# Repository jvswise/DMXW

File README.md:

# DMXW
DMX-512 wireless gateway to networked Moteino RFM69 (Arduino compatible) based slave devices suitable for running battery operated stage effects up to 300 metres from the gateway.

The gateway allows DMX-512 channels to be be redistributed to low-cost, customizable, battery-operated Moteino based slave nodes. Slaves have 4 analog (PWM) channels that can drive several amps each at 5 -12 Vdc. They have an additional two digital channels. 

There is prototype code, schematics, PCB files, and user manuals:
  - A configurable DMX-512 to DMXW gateway with optional manaul override
    controls (joystick, toggle switches, and potentiometers).
  - A generic remote slave node.
  - A specialized remote slave node for driving an LED pixel strip.
  - A test unit for either remote testing independent of a DMX-512 bus or
    for onboard testing of electronics that are to be connected to a generic
    or pixel strip node.

Folders:
  Arduino_sketches:
    - Arduino sketches for gateway, generic and remote slave nodes, and
      test unit.

  Documentation:
    - User manuals, schematics, PCB files, construction guides.

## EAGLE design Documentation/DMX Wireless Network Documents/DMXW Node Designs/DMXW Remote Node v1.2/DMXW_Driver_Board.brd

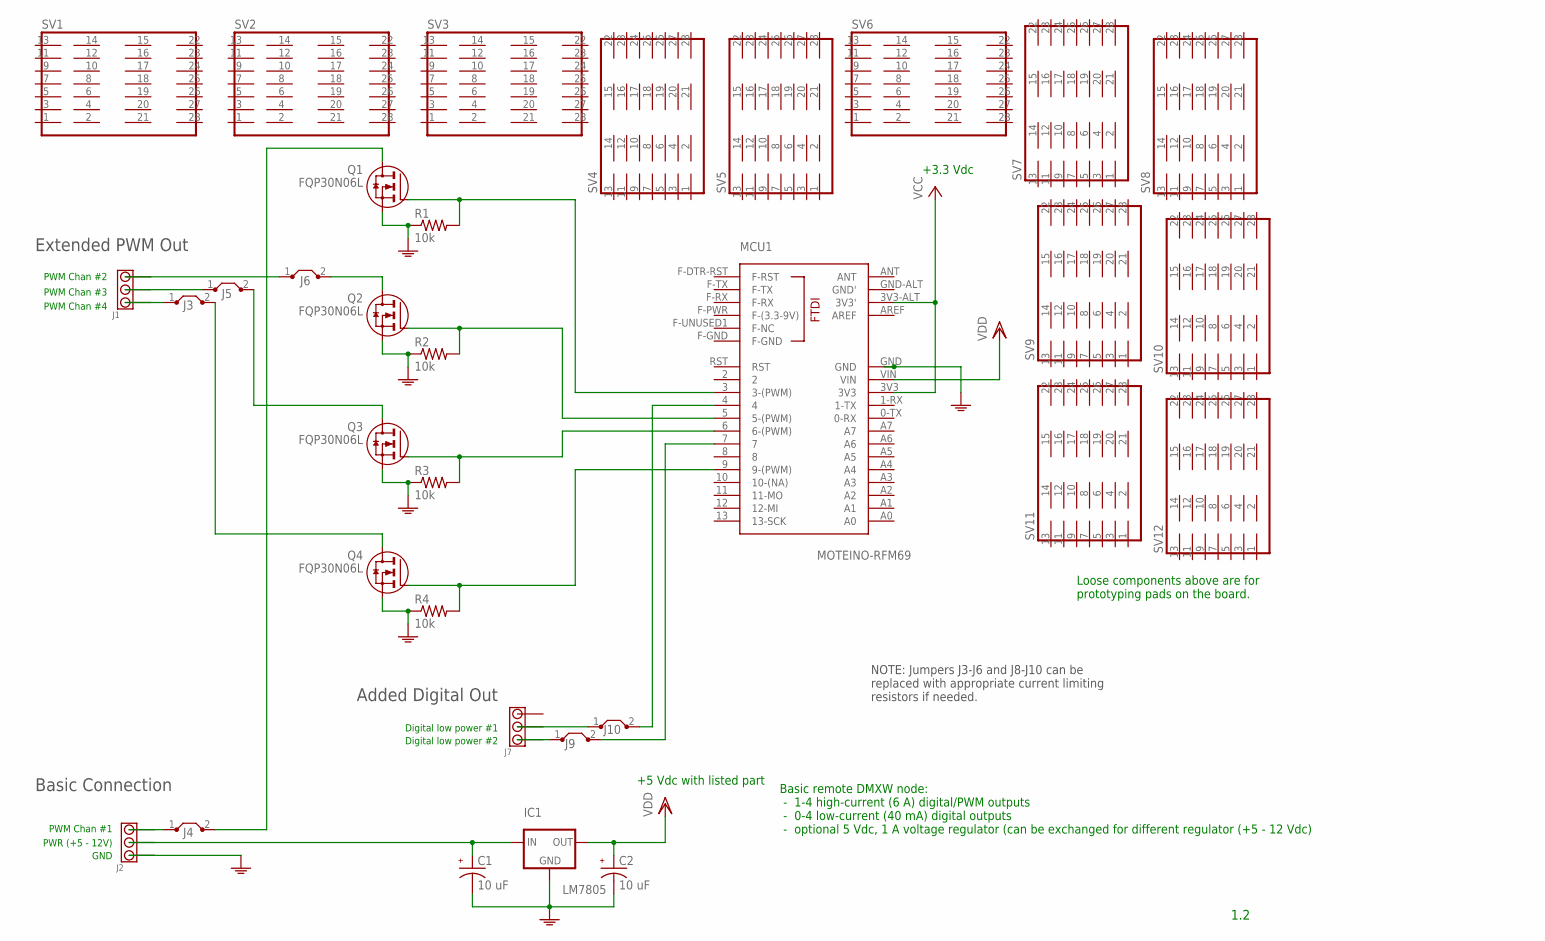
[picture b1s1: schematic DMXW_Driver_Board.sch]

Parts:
C1, C2: 10 uF; RADIAL-CANISTER
IC1: LM7805; TO-220
J1, J2, J7: TERMINAL-BLOCK-3; W237-103
J3, J4, J5, J6, J9, J10: J5MM; 05
MCU1: MOTEINO-RFM69; MOTEINO
Q1, Q2, Q3, Q4: FQP30N06L; TO-220
R1, R2, R3, R4: 10k; 0207/10
SV1, SV2, SV3, SV4, SV5, SV6, SV7, SV8, SV9, SV10, SV11, SV12: 14P

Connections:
GND: C1.-, C2.-, IC1.PIN2 (GND), J2.3, MCU1.GND, Q1.PIN3 (S), Q2.PIN3 (S), Q3.PIN3 (S), Q4.PIN3 (S), R1.1, R2.1, R3.1, R4.1
unnamed: MCU1.5 (5-(PWM)), Q2.PIN1 (G), R2.2
unnamed: J1.1, J6.1
unnamed: J1.2, J5.1
unnamed: J6.2, Q2.PIN2 (D)
unnamed: C1.+, IC1.PIN1 (IN), J2.2
unnamed: MCU1.6 (6-(PWM)), Q3.PIN1 (G), R3.2
unnamed: J5.2, Q3.PIN2 (D)
unnamed: MCU1.9 (9-(PWM)), Q4.PIN1 (G), R4.2
unnamed: J3.2, Q4.PIN2 (D)
unnamed: J10.2, MCU1.4
unnamed: MCU1.3 (3-(PWM)), Q1.PIN1 (G), R1.2
unnamed: J4.2, Q1.PIN2 (D)
unnamed: J9.2, MCU1.7
unnamed: J7.2, J10.1
unnamed: J2.1, J4.1
unnamed: J1.3, J3.1
unnamed: J7.3, J9.1
VCC: MCU1.3V3, MCU1.3V3-ALT (3V3')
VDD: C2.+, IC1.PIN3 (OUT), MCU1.VIN

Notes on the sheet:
PWR (+5 - 12V)
GND
PWM Chan #1
PWM Chan #4
PWM Chan #3
PWM Chan #2
Digital low power #2
Digital low power #1
1.2
+3.3 Vdc
Basic remote DMXW node: - 1-4 high-current (6 A) digital/PWM outputs - 0-4 low-current (40 mA) digital outputs - optional 5 Vdc, 1 A voltage regulator (can be exchanged for different regulator (+5 - 12 Vdc)
Basic Connection
Extended PWM Out
Added Digital Out
+5 Vdc with listed part
NOTE: Jumpers J3-J6 and J8-J10 can be replaced with appropriate current limiting resistors if needed.
Loose components above are for prototyping pads on the board.

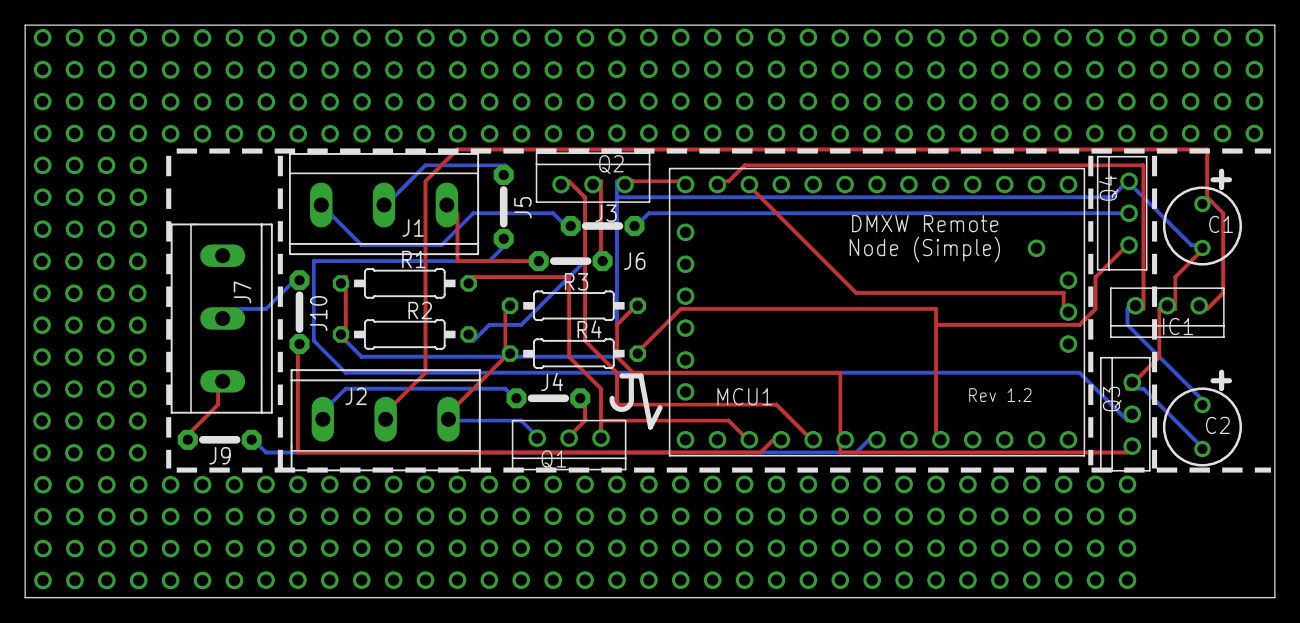
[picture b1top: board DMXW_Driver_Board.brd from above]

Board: 2 copper layers, 99.5 x 45.6 mm, 33 parts (0 on the bottom side), 20 nets.

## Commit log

2021-03-05 Added missing modified RFM69 library
